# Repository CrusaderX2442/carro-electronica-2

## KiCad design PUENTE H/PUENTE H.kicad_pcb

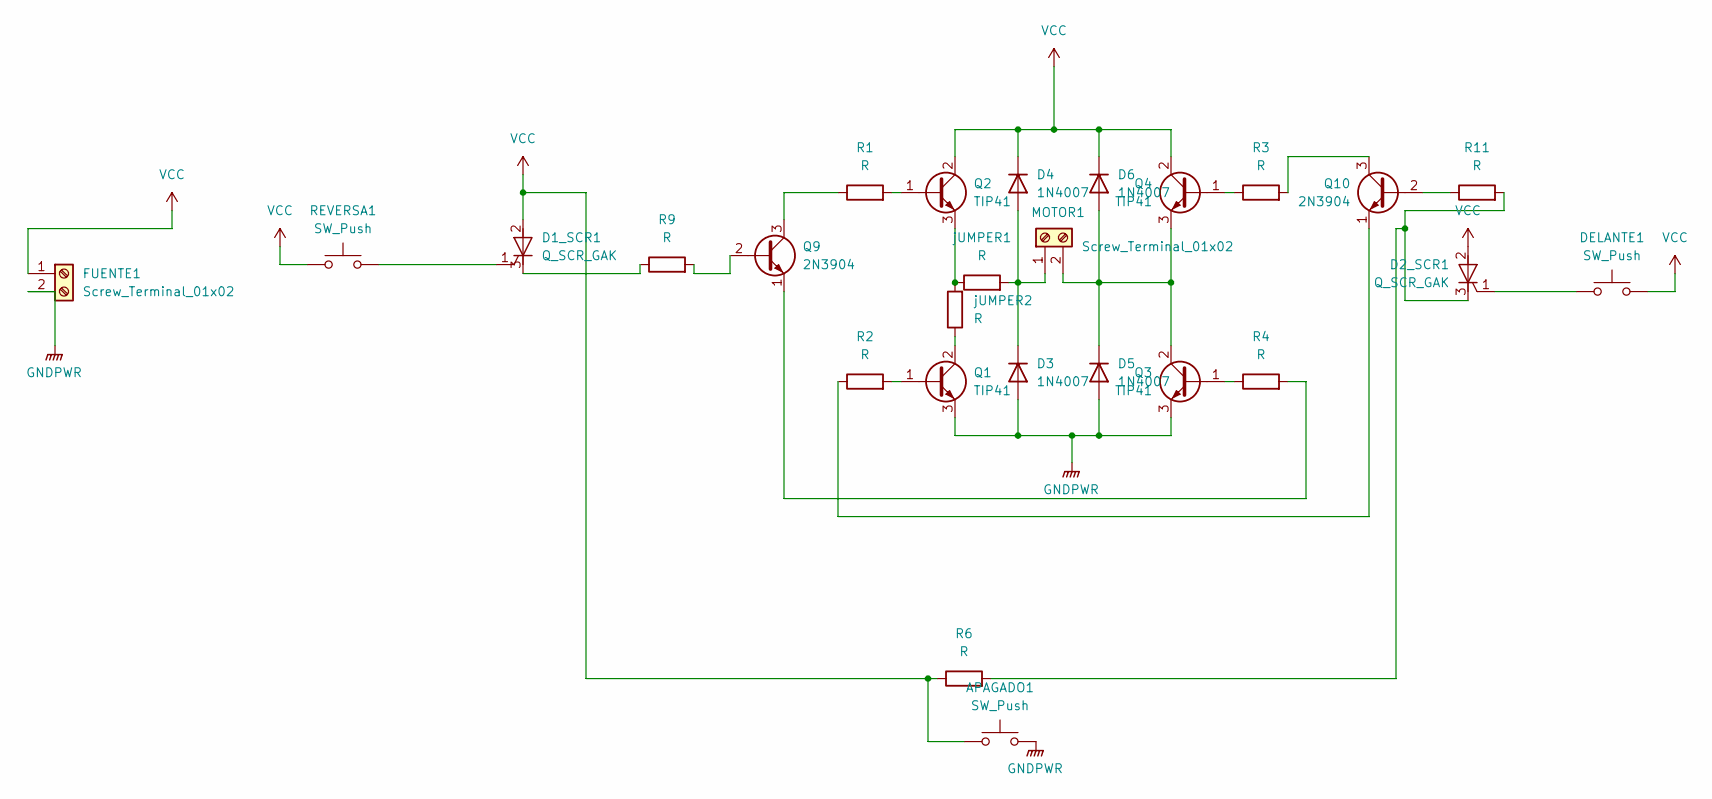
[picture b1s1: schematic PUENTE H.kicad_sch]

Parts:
APAGADO1: SW_Push; SW_PUSH_6mm_H7.3mm
D1_SCR1, D2_SCR1: Q_SCR_GAK; TO-220-3_Vertical
D3, D4, D5, D6: 1N4007; D_DO-41_SOD81_P12.70mm_Horizontal
DELANTE1: SW_Push; SW_PUSH_6mm_H7.3mm
FUENTE1: Screw_Terminal_01x02; JST_EH_B2B-EH-A_1x02_P2.50mm_Vertical
MOTOR1: Screw_Terminal_01x02; JST_EH_B2B-EH-A_1x02_P2.50mm_Vertical
Q1, Q2, Q3, Q4: TIP41; TO-220-3_Vertical
Q9, Q10: 2N3904; TO-92L_Wide
R1, R2, R3, R4, R6, R9, R11: R; R_Axial_DIN0309_L9.0mm_D3.2mm_P15.24mm_Horizontal
REVERSA1: SW_Push; SW_PUSH_6mm_H7.3mm
jUMPER1: R; R_Axial_DIN0309_L9.0mm_D3.2mm_P12.70mm_Horizontal
jUMPER2: R; R_Axial_DIN0309_L9.0mm_D3.2mm_P15.24mm_Horizontal

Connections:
GNDPWR: APAGADO1.2, D3.2 (A), D5.2 (A), FUENTE1.2, Q1.3 (E), Q3.3 (E); also elsewhere on the board
unnamed: D1_SCR1.1 (G), REVERSA1.2
unnamed: D1_SCR1.3 (K), R9.1
unnamed: D2_SCR1.1 (G), DELANTE1.2
unnamed: D2_SCR1.3 (K), R6.2, R11.2
unnamed 5: D3.1 (K), D4.2 (A), MOTOR1.1, jUMPER1.2; also elsewhere on the board
unnamed 6: D5.1 (K), D6.2 (A), MOTOR1.2, Q3.2 (C), Q4.3 (E); also elsewhere on the board
unnamed: Q1.1 (B), R2.2
unnamed: Q1.2 (C), jUMPER2.1
unnamed: Q2.1 (B), R1.2
unnamed: Q2.3 (E), jUMPER1.1, jUMPER2.2
unnamed: Q3.1 (B), R4.1
unnamed: Q4.1 (B), R3.1
unnamed: Q9.2 (B), R9.2
unnamed: Q9.3 (C), R1.1
unnamed: Q9.1 (E), R4.2
unnamed: Q10.2 (B), R11.1
unnamed: Q10.3 (C), R3.2
unnamed: Q10.1 (E), R2.1
VCC: APAGADO1.1, D1_SCR1.2 (A), D2_SCR1.2 (A), D4.1 (K), D6.1 (K), DELANTE1.1, FUENTE1.1, Q2.2 (C), Q4.2 (C), R6.1, REVERSA1.1; also elsewhere on the board

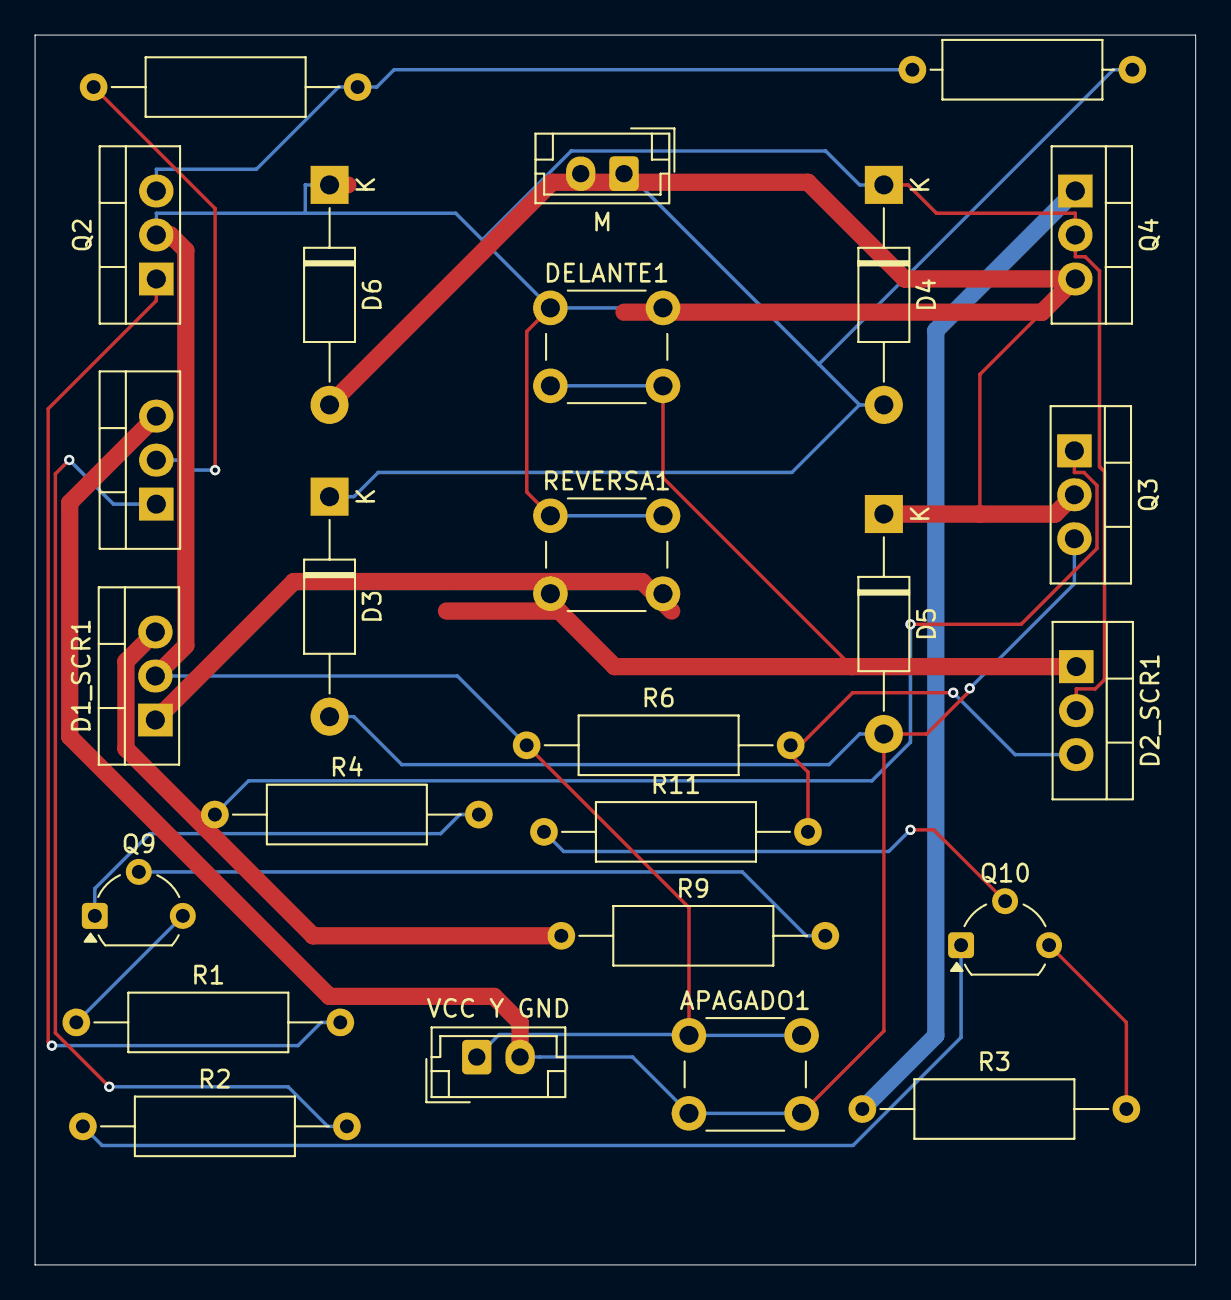
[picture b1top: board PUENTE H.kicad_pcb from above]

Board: 2 copper layers, 67.0 x 71.0 mm, 26 parts (0 on the bottom side), 20 nets.

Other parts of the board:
M: Screw_Terminal_01x02; JST_EH_B2B-EH-A_1x02_P2.50mm_Vertical
VCC Y GND: Screw_Terminal_01x02; JST_EH_B2B-EH-A_1x02_P2.50mm_Vertical

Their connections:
GNDPWR: VCC Y GND.2; also elsewhere on the board
unnamed 5: M.1; also elsewhere on the board
unnamed 6: M.2; also elsewhere on the board
VCC: VCC Y GND.1; also elsewhere on the board

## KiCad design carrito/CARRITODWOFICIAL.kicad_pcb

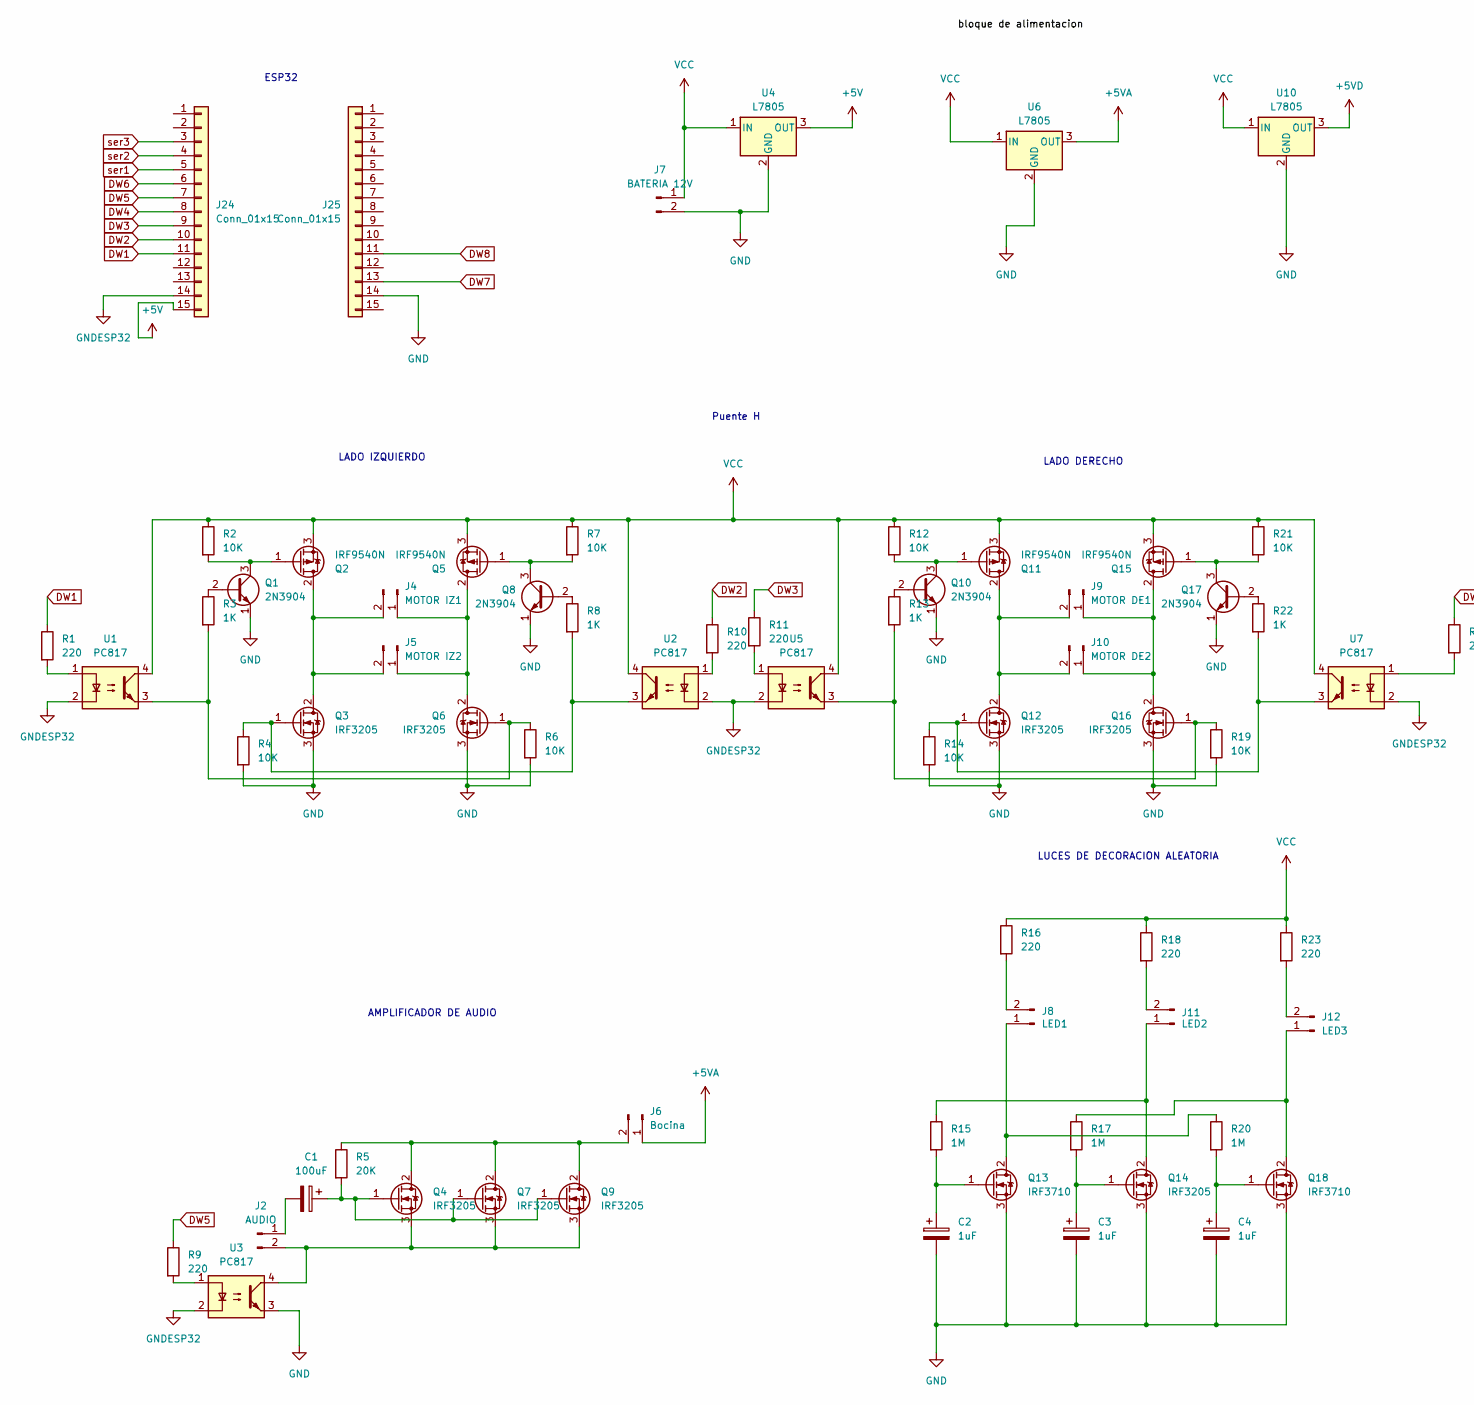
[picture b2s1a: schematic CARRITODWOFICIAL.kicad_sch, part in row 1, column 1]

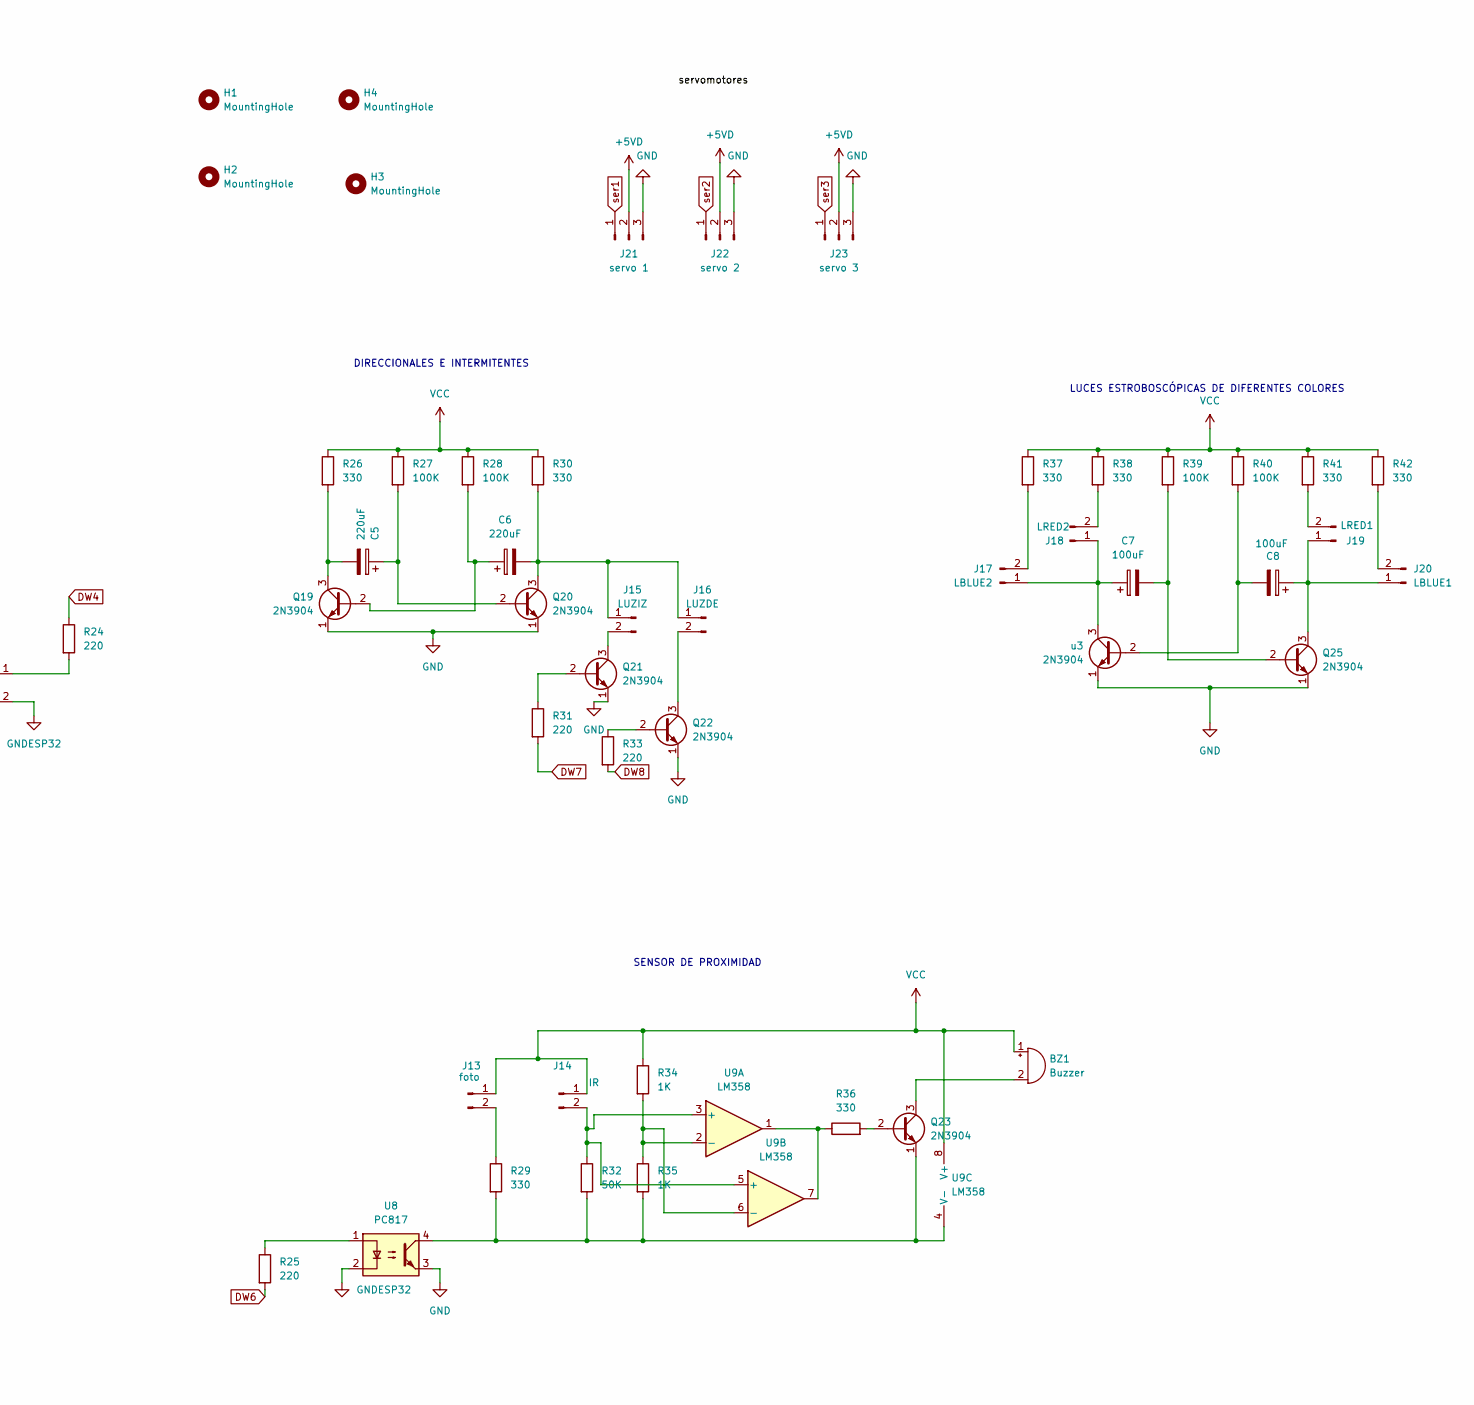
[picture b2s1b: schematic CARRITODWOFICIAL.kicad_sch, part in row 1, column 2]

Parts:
BZ1: Buzzer; Buzzer_12x9.5RM7.6; Lcsc Part C96256
C1, C7, C8: 100uF; CP_Radial_D5.0mm_P2.50mm; Lcsc Part C109392
C2, C3, C4: 1uF; CP_Radial_D5.0mm_P2.50mm; Lcsc Part C2927584
C5, C6: 220uF; CP_Radial_D6.3mm_P2.50mm; Lcsc Part C2831783
H1, H2, H3, H4: MountingHole; MountingHole_3.5mm
J2: AUDIO; Molex_KK-254_AE-6410-02A_1x02_P2.54mm_Vertical
J4: MOTOR IZ1; Molex_KK-254_AE-6410-02A_1x02_P2.54mm_Vertical
J5: MOTOR IZ2; Molex_KK-254_AE-6410-02A_1x02_P2.54mm_Vertical
J6: Bocina; Molex_KK-254_AE-6410-02A_1x02_P2.54mm_Vertical
J7: BATERIA 12V; Molex_KK-254_AE-6410-02A_1x02_P2.54mm_Vertical
J8: LED1; Molex_KK-254_AE-6410-02A_1x02_P2.54mm_Vertical
J9: MOTOR DE1; Molex_KK-254_AE-6410-02A_1x02_P2.54mm_Vertical
J10: MOTOR DE2; Molex_KK-254_AE-6410-02A_1x02_P2.54mm_Vertical
J11: LED2; Molex_KK-254_AE-6410-02A_1x02_P2.54mm_Vertical
J12: LED3; Molex_KK-254_AE-6410-02A_1x02_P2.54mm_Vertical
J13: foto; Molex_KK-254_AE-6410-02A_1x02_P2.54mm_Vertical
J14: IR; Molex_KK-254_AE-6410-02A_1x02_P2.54mm_Vertical
J15: LUZIZ; Molex_KK-254_AE-6410-02A_1x02_P2.54mm_Vertical
J16: LUZDE; Molex_KK-254_AE-6410-02A_1x02_P2.54mm_Vertical
J17: LBLUE2; Molex_KK-254_AE-6410-02A_1x02_P2.54mm_Vertical
J18: LRED2; Molex_KK-254_AE-6410-02A_1x02_P2.54mm_Vertical
J19: LRED1; Molex_KK-254_AE-6410-02A_1x02_P2.54mm_Vertical
J20: LBLUE1; Molex_KK-254_AE-6410-02A_1x02_P2.54mm_Vertical
J21: servo 1; Molex_KK-254_AE-6410-03A_1x03_P2.54mm_Vertical
J22: servo 2; Molex_KK-254_AE-6410-03A_1x03_P2.54mm_Vertical
J23: servo 3; Molex_KK-254_AE-6410-03A_1x03_P2.54mm_Vertical
J24, J25: Conn_01x15; PinSocket_1x15_P2.54mm_Vertical; Lcsc Part C55020533
Q1, Q8, Q10, Q17, Q19, Q20, Q21, Q22, Q23, Q25: 2N3904; TO-92_Inline; Lcsc Part C2874602
Q2, Q5, Q11, Q15: IRF9540N; TO-220-3_Vertical; Lcsc Part C2575
Q3, Q4, Q6, Q7, Q9, Q12, Q14, Q16: IRF3205; TO-220-3_Vertical; Lcsc Part C2561
Q13, Q18: IRF3710; TO-220-3_Vertical; Lcsc Part C2562
R1, R9, R10, R11, R16, R18, R23, R24, R25, R31, R33: 220; R_1206_3216Metric_Pad1.30x1.75mm_HandSolder; Lcsc Part C2907127
R2, R4, R6, R7, R12, R14, R19, R21: 10K; R_Axial_DIN0207_L6.3mm_D2.5mm_P7.62mm_Horizontal; Lcsc Part C57436
R3, R8, R13, R22: 1K; R_Axial_DIN0207_L6.3mm_D2.5mm_P7.62mm_Horizontal; Lcsc Part C57435
R5: 20K; R_1206_3216Metric_Pad1.30x1.75mm_HandSolder; Lcsc Part C49196669
R15, R17, R20: 1M; R_1206_3216Metric_Pad1.30x1.75mm_HandSolder; Lcsc Part C2907003
R26, R29, R30, R36, R37, R38, R41, R42: 330; R_1206_3216Metric_Pad1.30x1.75mm_HandSolder; Lcsc Part C125768
R27, R28, R39, R40: 100K; R_1206_3216Metric_Pad1.30x1.75mm_HandSolder; Lcsc Part C2907088
R32: 50K; R_1206_3216Metric_Pad1.30x1.75mm_HandSolder; Lcsc Part C2828840
R34, R35: 1K; R_1206_3216Metric_Pad1.30x1.75mm_HandSolder; Lcsc Part C2907002
U1, U2, U3, U5, U7, U8: PC817; SO-4_4.4x3.6mm_P2.54mm; Lcsc Part C66405
U4, U6, U10: L7805; TO-220-3_Vertical; Lcsc Part TO-220ST
U9: LM358; SOIC-8_3.9x4.9mm_P1.27mm; Lcsc Part C5296727
u3: 2N3904; TO-92_Inline; Lcsc Part C2874602

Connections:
+5V: J24.15, U4.3 (OUT)
+5VA: J6.1, U6.3 (OUT)
+5VD: J21.2, J22.2, J23.2, U10.3 (OUT)
DW1: J24.11, R1.1
DW2: J24.10, R10.1
DW3: J24.9, R11.1
DW4: J24.8, R24.1
DW5: J24.7, R9.1
DW6: J24.6, R25.2
DW7: J25.13, R31.2
DW8: J25.11, R33.2
GND: C2.2, C3.2, C4.2, J7.2, J21.3, J22.3, J23.3, J25.14, Q1.1 (E), Q3.3 (S), Q6.3 (S), Q8.1 (E), Q10.1 (E), Q12.3 (S), Q13.3 (S), Q14.3 (S), Q16.3 (S), Q17.1 (E), Q18.3 (S), Q19.1 (E), Q20.1 (E), Q21.1 (E), Q22.1 (E), Q25.1 (E), R4.2, R6.2, R14.2, R19.2, U3.3, U4.2 (GND), U6.2 (GND), U8.3, U10.2 (GND), u3.1 (E); also elsewhere on the board
GNDESP32: J24.14, U1.2, U2.2, U3.2, U5.2, U7.2, U8.2
unnamed: BZ1.2 (-), Q23.3 (C)
unnamed: C1.2, J2.1
unnamed: J2.2, Q4.3 (S), Q7.3 (S), Q9.3 (S), U3.4
unnamed: J4.1, J5.1, Q5.2 (D), Q6.2 (D)
unnamed: J4.2, J5.2, Q2.2 (D), Q3.2 (D)
unnamed: J6.2, Q4.2 (D), Q7.2 (D), Q9.2 (D), R5.1
unnamed: J8.1, Q13.2 (D), R20.1
unnamed: J8.2, R16.2
unnamed: J9.1, J10.1, Q15.2 (D), Q16.2 (D)
unnamed: J9.2, J10.2, Q11.2 (D), Q12.2 (D)
unnamed: J11.1, Q14.2 (D), R15.1
unnamed: J11.2, R18.2
unnamed: J12.1, Q18.2 (D), R17.1
unnamed: J12.2, R23.2
unnamed: J13.2, R29.1
unnamed: J14.2, R32.1, U9.3 (+), U9.5 (+)
unnamed: C6.2, J15.1, J16.1, Q20.3 (C), R30.2
unnamed: J15.2, Q21.3 (C)
unnamed: J16.2, Q22.3 (C)
unnamed 32: C7.1, J17.1, J18.1, u3.3 (C); also elsewhere on the board
unnamed: J17.2, R37.2
unnamed: J18.2, R38.2
unnamed: C8.1, J19.1, J20.1, Q25.3 (C)
unnamed: J19.2, R41.2
unnamed: J20.2, R42.2
unnamed: Q1.2 (B), R3.1
unnamed: Q1.3 (C), Q2.1 (G), R2.2
unnamed: Q3.1 (G), R4.1, R8.2, U2.3
unnamed: C1.1, Q4.1 (G), Q7.1 (G), Q9.1 (G), R5.2
unnamed: Q5.1 (G), Q8.3 (C), R7.2
unnamed: Q6.1 (G), R3.2, R6.1, U1.3
unnamed: Q8.2 (B), R8.1
unnamed: Q10.2 (B), R13.1
unnamed: Q10.3 (C), Q11.1 (G), R12.2
unnamed: Q12.1 (G), R14.1, R22.2, U7.3
unnamed: C2.1, Q13.1 (G), R15.2
unnamed: C3.1, Q14.1 (G), R17.2
unnamed: Q15.1 (G), Q17.3 (C), R21.2
unnamed: Q16.1 (G), R13.2, R19.1, U5.3
unnamed: Q17.2 (B), R22.1
unnamed: C4.1, Q18.1 (G), R20.2
unnamed: C6.1, Q19.2 (B), R28.2
unnamed: C5.2, Q19.3 (C), R26.2
unnamed: C5.1, Q20.2 (B), R27.2
unnamed: Q21.2 (B), R31.1
unnamed: Q22.2 (B), R33.1
unnamed: Q23.2 (B), R36.2
unnamed: Q23.1 (E), R29.2, R32.2, R35.2, U8.4, U9.4 (V-)
unnamed 61: C8.2, R40.2, u3.2 (B); also elsewhere on the board
unnamed: C7.2, Q25.2 (B), R39.2
unnamed: R1.2, U1.1
unnamed: R9.2, U3.1
unnamed: R10.2, U2.1
unnamed: R11.2, U5.1
unnamed: R24.2, U7.1
unnamed: R25.1, U8.1
unnamed: R36.1, U9.1, U9.7
unnamed: R34.2, R35.1, U9.2 (-), U9.6 (-)
VCC: BZ1.1 (+), J7.1, J13.1, J14.1, Q2.3 (S), Q5.3 (S), Q11.3 (S), Q15.3 (S), R2.1, R7.1, R12.1, R16.1, R18.1, R21.1, R23.1, R26.1, R27.1, R28.1, R30.1, R34.1, R37.1, R38.1, R39.1, R40.1, R41.1, R42.1, U1.4, U2.4, U4.1 (IN), U5.4, U6.1 (IN), U7.4, U9.8 (V+), U10.1 (IN)
ser1: J21.1, J24.5
ser2: J22.1, J24.4
ser3: J23.1, J24.3

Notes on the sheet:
DIRECCIONALES E INTERMITENTES
SENSOR DE PROXIMIDAD
LADO DERECHO
ESP32
LADO IZQUIERDO
AMPLIFICADOR DE AUDIO
LUCES ESTROBOSCÓPICAS DE DIFERENTES COLORES
Puente H
LUCES DE DECORACION ALEATORIA

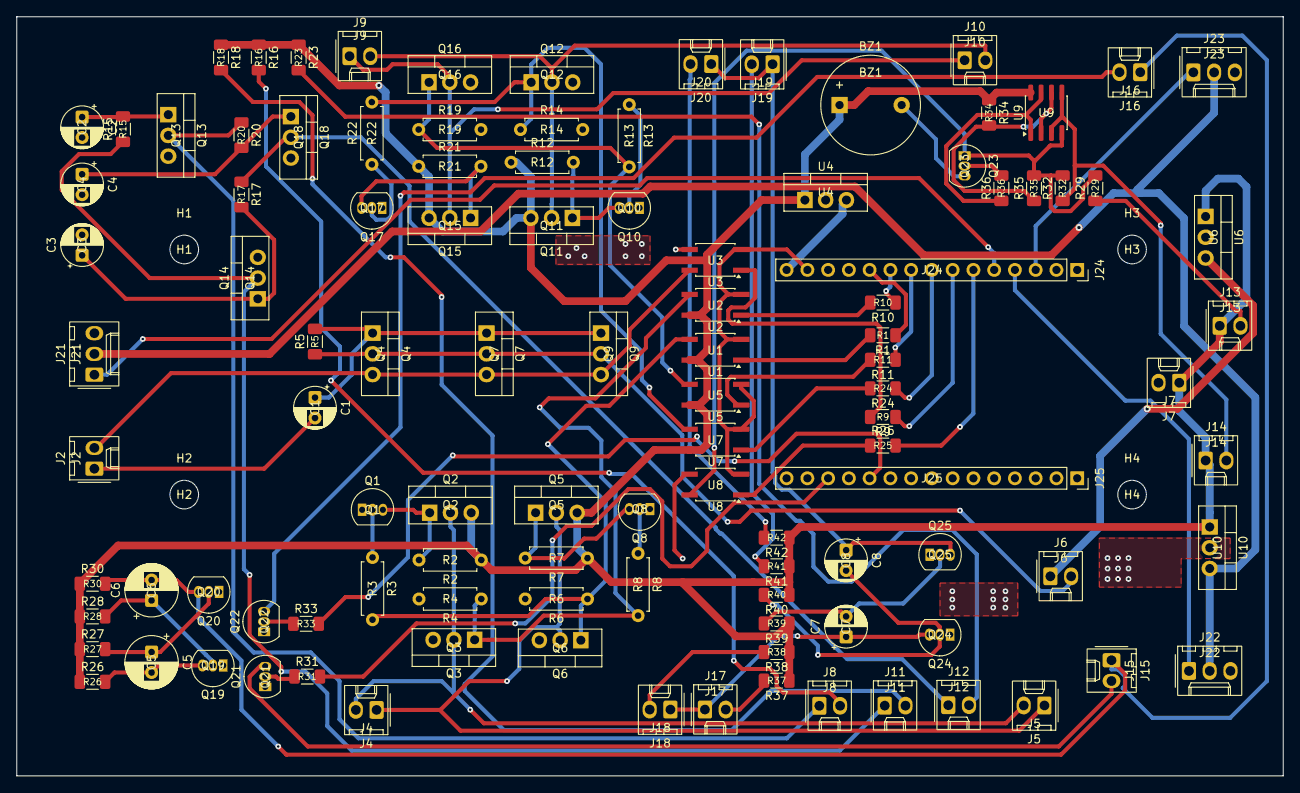
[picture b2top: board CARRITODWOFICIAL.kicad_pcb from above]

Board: 2 copper layers, 155.0 x 92.9 mm, 113 parts (0 on the bottom side), 75 nets.

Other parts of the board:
Q24: 2N3904; TO-92_Inline

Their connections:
GND: Q24.1 (E); also elsewhere on the board
unnamed 32: Q24.3 (C); also elsewhere on the board
unnamed 61: Q24.2 (B); also elsewhere on the board

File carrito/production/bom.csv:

Designator,Footprint,Quantity,Value,LCSC Part #
BZ1,Buzzer_12x9.5RM7.6,1,Buzzer,
"C1, C7, C8",CP_Radial_D5.0mm_P2.50mm,3,100uF,
"C2, C3, C4",CP_Radial_D5.0mm_P2.50mm,3,1uF,
"C5, C6",CP_Radial_D6.3mm_P2.50mm,2,220uF,
J10,Molex_KK-254_AE-6410-02A_1x02_P2.54mm_Vertical,1,MOTOR DE2,
J11,Molex_KK-254_AE-6410-02A_1x02_P2.54mm_Vertical,1,LED2,
J12,Molex_KK-254_AE-6410-02A_1x02_P2.54mm_Vertical,1,LED3,
J13,Molex_KK-254_AE-6410-02A_1x02_P2.54mm_Vertical,1,foto,
J14,Molex_KK-254_AE-6410-02A_1x02_P2.54mm_Vertical,1,IR,
J15,Molex_KK-254_AE-6410-02A_1x02_P2.54mm_Vertical,1,LUZIZ,
J16,Molex_KK-254_AE-6410-02A_1x02_P2.54mm_Vertical,1,LUZDE,
J17,Molex_KK-254_AE-6410-02A_1x02_P2.54mm_Vertical,1,LBLUE2,
J18,Molex_KK-254_AE-6410-02A_1x02_P2.54mm_Vertical,1,LRED2,
J19,Molex_KK-254_AE-6410-02A_1x02_P2.54mm_Vertical,1,LRED1,
J2,Molex_KK-254_AE-6410-02A_1x02_P2.54mm_Vertical,1,AUDIO,
J20,Molex_KK-254_AE-6410-02A_1x02_P2.54mm_Vertical,1,LBLUE1,
J21,Molex_KK-254_AE-6410-03A_1x03_P2.54mm_Vertical,1,servo 1,
J22,Molex_KK-254_AE-6410-03A_1x03_P2.54mm_Vertical,1,servo 2,
J23,Molex_KK-254_AE-6410-03A_1x03_P2.54mm_Vertical,1,servo 3,
"J24, J25",PinSocket_1x15_P2.54mm_Vertical,2,Conn_01x15,
J4,Molex_KK-254_AE-6410-02A_1x02_P2.54mm_Vertical,1,MOTOR IZ1,
J5,Molex_KK-254_AE-6410-02A_1x02_P2.54mm_Vertical,1,MOTOR IZ2,
J6,Molex_KK-254_AE-6410-02A_1x02_P2.54mm_Vertical,1,Bocina,
J7,Molex_KK-254_AE-6410-02A_1x02_P2.54mm_Vertical,1,BATERIA 12V,
J8,Molex_KK-254_AE-6410-02A_1x02_P2.54mm_Vertical,1,LED1,
J9,Molex_KK-254_AE-6410-02A_1x02_P2.54mm_Vertical,1,MOTOR DE1,
"Q1, Q10, Q17, Q19, Q20, Q21, Q22, Q23, Q24, Q25, Q8",TO-92_Inline,11,2N3904,
"Q11, Q15, Q2, Q5",TO-220-3_Vertical,4,IRF9540N,
"Q12, Q14, Q16, Q3, Q4, Q6, Q7, Q9",TO-220-3_Vertical,8,IRF3205,
"Q13, Q18",TO-220-3_Vertical,2,IRF3710,
"R1, R10, R11, R16, R18, R23, R24, R25, R31, R33, R9",1206,11,220,
"R12, R14, R19, R2, R21, R4, R6, R7",R_Axial_DIN0207_L6.3mm_D2.5mm_P7.62mm_Horizontal,8,10K,
"R13, R22, R3, R8",R_Axial_DIN0207_L6.3mm_D2.5mm_P7.62mm_Horizontal,4,1K,
"R15, R17, R20",1206,3,1M,
"R26, R29, R30, R36, R37, R38, R41, R42",1206,8,330,
"R27, R28, R39, R40",1206,4,100k,
R32,1206,1,50K,
"R34, R35",1206,2,1K,
R5,1206,1,20K,
"U1, U2, U3, U5, U7, U8",SO-4_4.4x3.6mm_P2.54mm,6,PC817,
"U10, U4, U6",TO-220-3_Vertical,3,L7805,
U9,SOIC-8_3.9x4.9mm_P1.27mm,1,LM358,
